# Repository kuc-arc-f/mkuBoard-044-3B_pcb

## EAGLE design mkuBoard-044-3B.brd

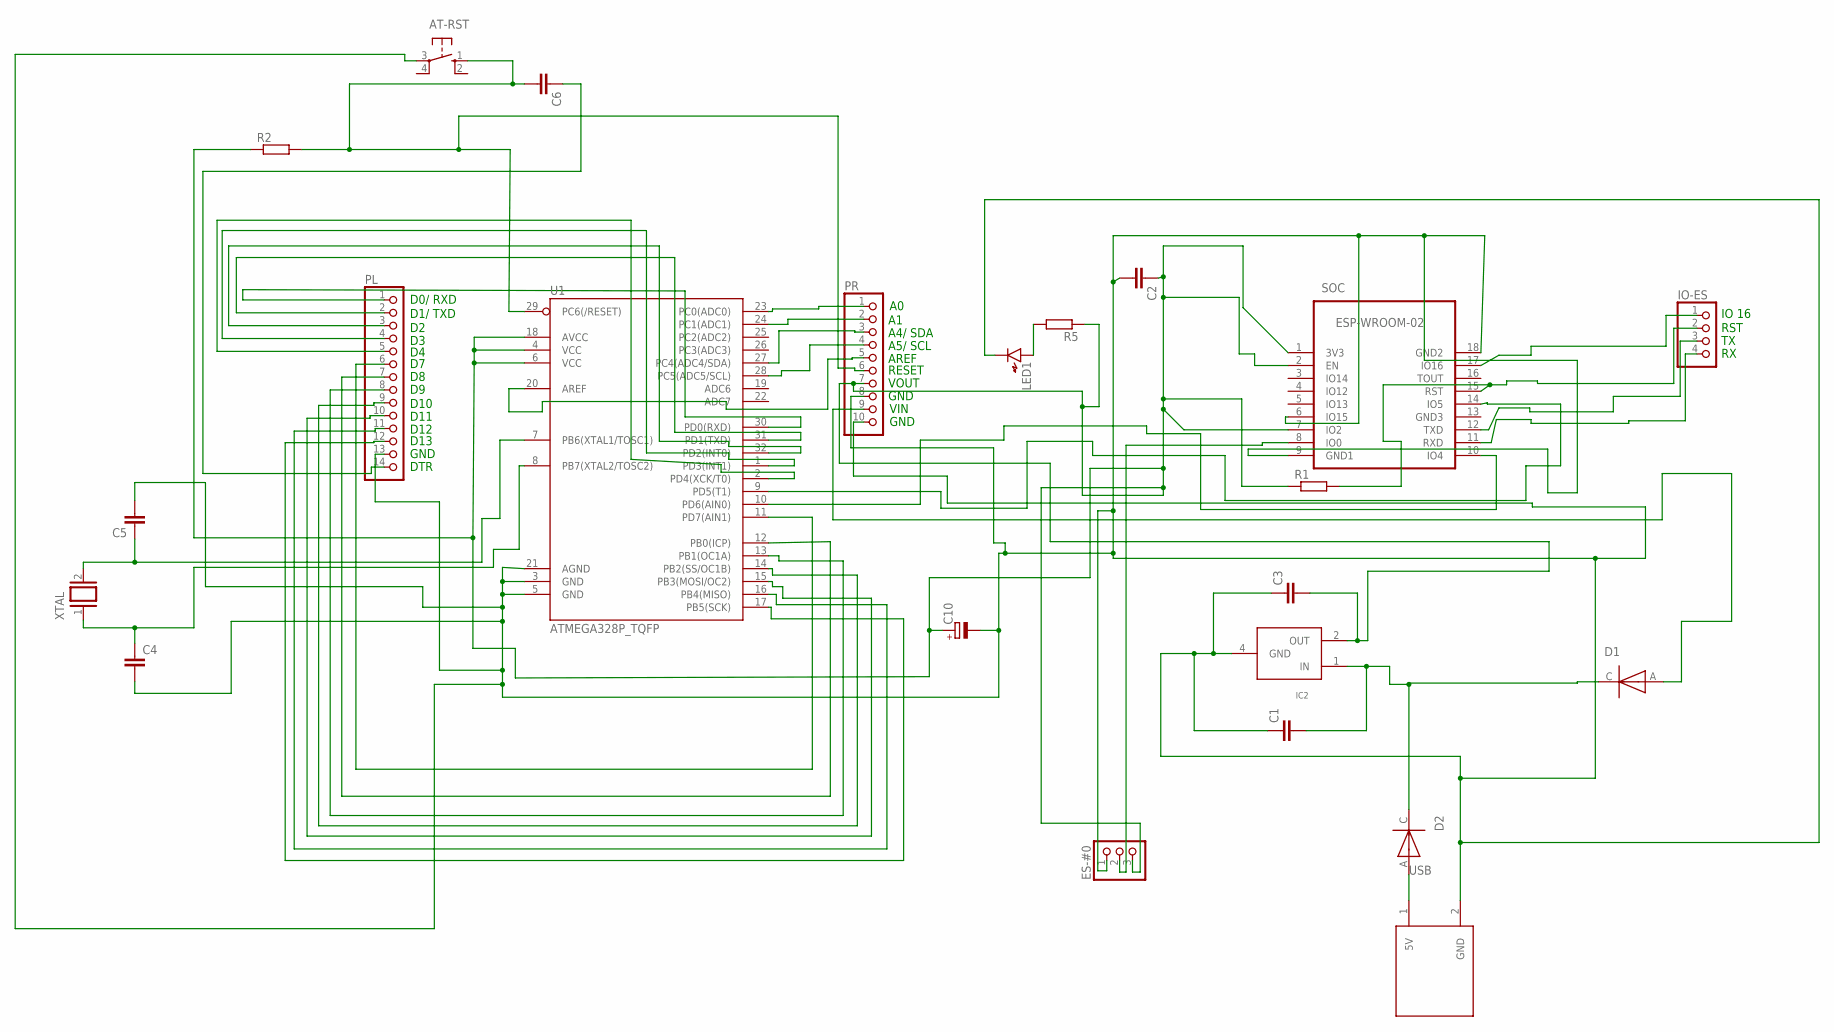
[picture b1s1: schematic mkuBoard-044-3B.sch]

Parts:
AT-RST: 10-XX; B3F-10XX
C1, C2, C4, C5, C6: C-EUC0603; C0603
C3: C-EUC1206; C1206
C10: CPOL-EU153CLV-0605; 153CLV-0605
D1, D2: DIODE-EX; SOD80C
ES-#0: PINHD-1X3; 1X03
IC2: NJM2845DL1; NJM2845DL1-PKG
IO-ES: PINHD-1X4; 1X04
LED1: LED1608
PL: PINHD-1X14; 1X14
PR: PINHD-1X10; 1X10
R1, R2, R5: R-EU_R0603; R0603
SOC: ESP-WROOM-02; FRONT-FACE-CP2
U1: ATMEGA328P_TQFP; TQFP32-08
USB: USB-CUST-1; USB-CUST-1-PKG
XTAL: XTAL/S; QS

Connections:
unnamed: ES-#0.2, SOC.8 (IO0)
unnamed: PL.1, U1.30 (PD0(RXD))
unnamed: SOC.14 (IO5), U1.9 (PD5(T1))
unnamed: IO-ES.2, R1.2, SOC.15 (RST)
unnamed: C1.2, D1.C, D2.C, IC2.1 (IN)
unnamed: IO-ES.1, SOC.17 (IO16)
unnamed: D1.A, PR.9
unnamed: PR.3, U1.27 (PC4(ADC4/SDA))
unnamed: IO-ES.3, SOC.12 (TXD)
unnamed: IO-ES.4, SOC.11 (RXD)
unnamed: PR.4, U1.28 (PC5(ADC5/SCL))
unnamed: D2.A, USB.1 (5V)
unnamed: C2.1, C3.2, C10.+, ES-#0.3, IC2.2 (OUT), PR.7, R1.1, R2.1, R5.1, SOC.1 (3V3), SOC.2 (EN), SOC.7 (IO2), U1.4 (VCC), U1.6 (VCC), U1.18 (AVCC)
unnamed: C6.1, PL.14
unnamed: PL.2, U1.31 (PD1(TXD))
unnamed: PL.3, U1.32 (PD2(INT0))
unnamed: PL.4, U1.1 (PD3(INT1))
unnamed: PL.5, U1.2 (PD4(XCK/T0))
unnamed: LED1.A, R5.2
unnamed: SOC.10 (IO4), U1.10 (PD6(AIN0))
unnamed: PL.6, U1.11 (PD7(AIN1))
unnamed: PL.7, U1.12 (PB0(ICP))
unnamed: PL.8, U1.13 (PB1(OC1A))
unnamed: PL.9, U1.14 (PB2(SS/OC1B))
unnamed: PL.10, U1.15 (PB3(MOSI/OC2))
unnamed: PL.11, U1.16 (PB4(MISO))
unnamed: PL.12, U1.17 (PB5(SCK))
unnamed: PR.1, U1.23 (PC0(ADC0))
unnamed: PR.2, U1.24 (PC1(ADC1))
unnamed: AT-RST.1 (S), C6.2, PR.6, R2.2, U1.29 (PC6(/RESET))
unnamed: AT-RST.3, C1.1, C2.2, C3.1, C4.2, C5.2, C10.-, ES-#0.1, IC2.4 (GND), LED1.K, PL.13, PR.8, PR.10, SOC.6 (IO15), SOC.9 (GND1), SOC.18 (GND2), U1.3 (GND), U1.5 (GND), U1.21 (AGND), USB.2 (GND)
unnamed: PR.5, U1.20 (AREF)
unnamed: C5.1, U1.7 (PB6(XTAL1/TOSC1)), XTAL.2
unnamed: C4.1, U1.8 (PB7(XTAL2/TOSC2)), XTAL.1

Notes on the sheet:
D0/ RXD
D1/ TXD
DTR
GND
D10
D11
D12
D13
A4/ SDA
A5/ SCL
AREF
RESET
VOUT
VIN
IO 16
RST

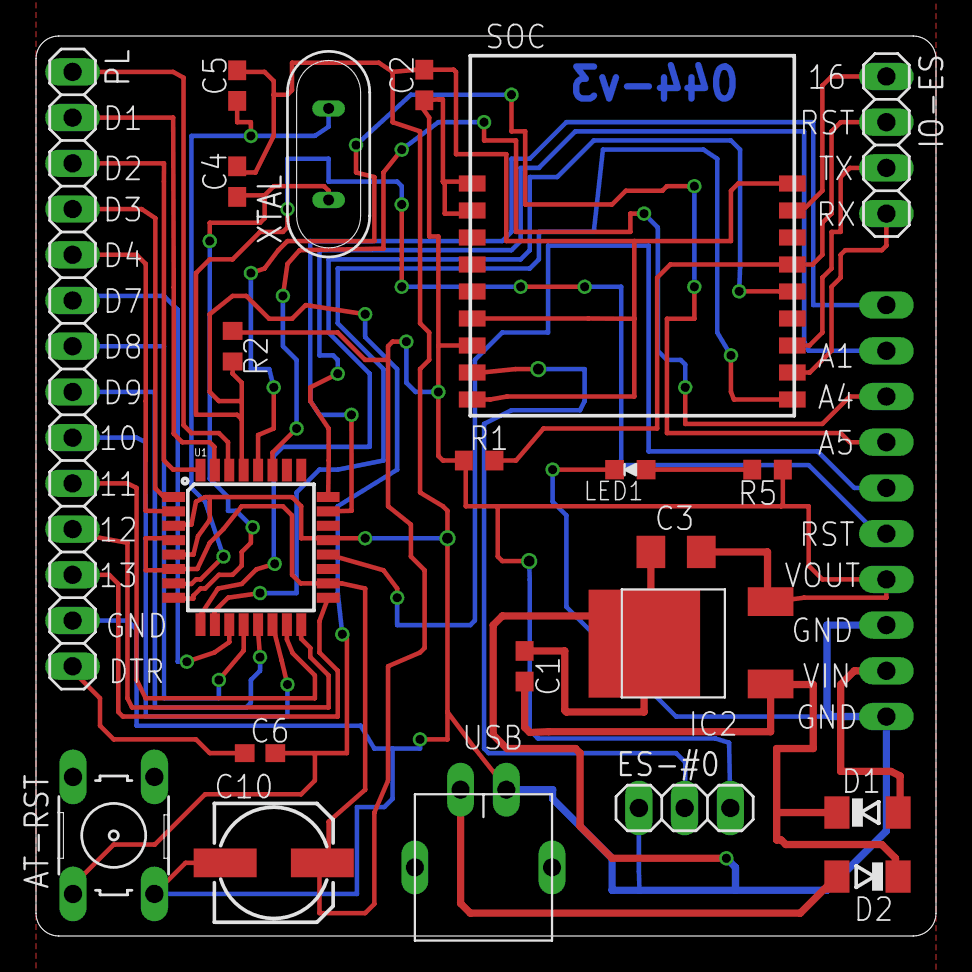
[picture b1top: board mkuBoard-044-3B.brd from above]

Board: 2 copper layers, 50.0 x 50.0 mm, 23 parts (1 on the bottom side), 34 nets.

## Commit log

2017-08-17 new, 08-17a1

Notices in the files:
parts and their libraries:
SparkFun-DigitalIC: Licensing: Creative Commons ShareAlike 4.0 International - https://creativecommons.org/licenses/by-sa/4.0
